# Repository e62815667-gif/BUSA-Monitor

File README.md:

# BUSA-Monitor

Исходные коды, интерфейсы, GitHub Actions и документация проекта «БУСА-1М №001».

## Актуальное состояние (15 ноября 2026)

**Ветка `main` — документация и текущая публикация. 22 активные ветки.** Исторические исходники всех 137 веток, находившихся в репозитории перед массовой очисткой, сохранены в проверенном Git-архиве.

- [Паспорт последней подтверждённой рабочей UI16](docs/UI16_VERIFIED_2026-11-15.md) — SHA-256, два BIN, статус проверки на оборудовании, ограничение по исходникам.
- [Актуальный реестр 22 веток](docs/BRANCH_INVENTORY_2026-11-15.md).
- [Полный отчёт об уборке](docs/REPOSITORY_AUDIT_2026-11-15.md).
- [Постоянный Git-архив из 137 веток](https://github.com/e62815667-gif/BUSA-Monitor/releases/tag/busa-git-backup-all-branches-20261115) — полный Git bundle, SHA, инструкция восстановления.
- [GitHub Actions](https://github.com/e62815667-gif/BUSA-Monitor/actions) — журналы сборок.
- [GitHub Releases](https://github.com/e62815667-gif/BUSA-Monitor/releases) — опубликованные релизы.
- [Открытые Pull Request](https://github.com/e62815667-gif/BUSA-Monitor/pulls) — 7 PR и все их необходимые ветки сохранены.
- [Правила проекта](PROJECT_RULES.md).

## Эталон UI16

**BUSA UI16 успешно установлена и работает на ESP32-S3 N16R8 по подтверждению владельца от 15.11.2026.** Оба BIN-файла (USB MERGED, APP OTA) находятся в Google Диске «успех буса». Контрольные суммы проверены.

Точная исходная ветка UI16 ещё не установлена. В GitHub сохранена более ранняя CALC4/WIFI1, но её нельзя автоматически считать исходниками UI16. Успешная сборка CI и работа прошивки на реальном устройстве — разные уровни проверки.

## Исторические ветки

140 → **22 активные**, 118 удалены из списка веток. Из них 115 удалены **после** создания и тестового восстановления постоянного Git-архива; первые 3 были точным дубликатом или принадлежали уже объединённым PR. Исходники доступны через восстановление из архива, не теряйте архивный релиз.

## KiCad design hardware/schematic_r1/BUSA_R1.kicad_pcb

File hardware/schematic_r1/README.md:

# БУСА — схема R1, 08.11.2026

Статус: **электрический проект, проверенный программно; не испытан на устройстве; не разрешение на производство PCB**. Основа — UI12 f80e8af, фактическая 44-контактная таблица ESP32 пользователя, фотографии модулей и уточнение VCC экрана = 3,3 В. Прошивка этой работой не менялась.

## Что изготовлено

- BUSA_R1.kicad_sch / BUSA_R1.kicad_pro / BUSA.kicad_sym / sym-lib-table — открываемый проект KiCad 9, с собственной библиотекой функциональных символов модулей.
- output/BUSA_R1_review.pdf — пояснения, разъёмы и схема по читаемым разделам.
- output/BUSA_R1.pdf — полный лист A1.
- output/NETLIST.xml и PIN_NETS.csv — список соединений, экспортированный KiCad.
- output/ERC.json — 0 ошибок, 0 предупреждений, исключений проверок нет.
- output/CHECKS.json — 10 независимых проверок экспортированных цепей; отрицательный контроль действительно обнаруживает соединение двух GPIO-выходов.
- output/BOM.csv и HEADER_44.csv — элементы и положение контактов ESP32. Наличие позиции в BOM не означает, что она уже есть у пользователя.
- BUSA_R1.kicad_pcb, BUSA.pretty, fp-lib-table и footprints.json — физический инженерный проект: 120 × 100 мм, два слоя, 67 электрических посадочных мест и четыре отверстия. Междурядье ESP32 25,50 мм взято с предоставленной пользователем переходной платы; шаг 2,54 мм — из его ответа. Геометрия PCF8575 пока предварительная.
- output/PCB_DRC.json, PCB_CHECKS.json и PCB_DRC_negative_control.json — полный DRC с сопоставлением схемы и платы, сверка 207 подключённых площадок по XML и испытание проверки настоящим коротким замыканием в временной копии.
- output/BUSA_R1_PCB_REVIEW.pdf, PCB_PREVIEW.png, MEASUREMENT_GUIDE.png, CONTROL_TEMPLATE_1TO1.pdf, BOM_REVIEW.csv, HARNESS.csv и ACCESSORIES.csv — документы для технической проверки. Это ещё не производственный FAB/ASSEMBLY.
- PRODUCTION.md и output/RELEASE_STATUS.json — выбранный изготовитель, проектные требования, состав будущего заказа и открытые условия готовности.

Символы пользовательских модулей являются функциональным описанием их выводов. Схемы внутри готовых модулей не воспроизведены и не проверены по изображению. Рисунок предыдущего эскиза не использовался как источник распиновки или размеров.

## Изменения по сравнению с картинкой

1. Вход питания J1 имеет ровно два контакта: 1 = +12 В, 2 = GND. Третьего провода нет.
2. ESP32 — настоящий вариант 44 PIN / два USB. Номера L01..L22 и R01..R22 идут сверху вниз при обоих USB наверху и виде на компоненты.
3. PCF8575 — готовый съёмный модуль, логика 3,3 В, SDA40/SCL41. INT не подключён. Клавиатура имеет девять сигнальных проводников.
4. Температуры: Вода GPIO16, Куб GPIO18, Колонна GPIO17, Авария GPIO21; по одной подтяжке 4,7 кОм и разъёму на канал, без DS2482. Порядок датчиков на разъёмах соответствует запрошенному отображению, а GPIO — текущей прошивке.
5. На модуль четырёх звуковых реле идут GND, IN1, IN2, IN3, IN4, VCC (шесть контактов логики); питание катушек JD-VCC проходит отдельно. Не путать эти линии с тремя переключаемыми контактами COM/NO/NC каждого реле. Силовые/сетевые нагрузки не входят в проект.
6. SN74LVC07A — новый, предлагаемый для несущей платы неинвертирующий буфер с открытым стоком. Сохраняет активный LOW из UI12, отводит 5 В от ESP32, обеспечивает подтяжки отключённого состояния. При выключенном питании логики используется Ioff по документации TI.
7. YF-S401 подключается через отдельный преобразователь уровня BC847B + триггер Шмитта, а не непосредственно к GPIO15. Сочетание двух инверсий сохраняет полярность и число импульсов. GPIO1 подготовлен только как аппаратный резерв отбора; в UI12 чтение отбора ещё не реализовано, модель датчика пока не выбрана.
8. Предлагаемый стабилизатор U2 R-78E5.0-1.0 — новая позиция для питания платы, а не выданная за имеющийся модуль с фотографии. Его можно заменить реальным существующим DC/DC только после установления модели, параметров и распиновки.

## Проверки, уже выполненные

KiCad 9.0.2 ERC без исключений: **0 нарушений**. Все соединения проверяются по NETLIST.xml, не только по внутренней модели генератора. Сверены 4 температурных канала, 5 TFT-сигналов, 4 релейных управляющих сигнала, I²C, питание и разделение каналов импульсов. USB19/20, PSRAM35/36/37 и загрузочные выводы оставлены неиспользованными.

Негативный тест: в временной копии GPIO7 соединён с GPIO14; KiCad вернул ошибку конфликта выходов. Исходный проект после теста остаётся без этого замыкания.

Для импульсного входа рассчитано: при источнике 4,5 В, резисторах с допуском 1% и предположении VBE=0,85 В базовый ток не менее 104 мкА, ток коллектора не более 0,702 мА, принудительный коэффициент около 6,72. Это проверка запаса насыщения для принятой модели входа, не замена измерению реального датчика. RC-цепь имеет постоянную времени менее 6 мкс против типового периода 1,7 мс при 588 Гц. Номинальные 98 Гц/(л/мин) взяты из существующей прошивки; их физическая точность не подтверждена.

Подтяжки R1/R2 I²C — опциональные. На готовом PCF8575 могут уже быть резисторы; до установки нужно проверить результирующее сопротивление к 3,3 В. Не устанавливать подтяжки к 5 В.

## Границы проверки и следующие измерения

- **Релейный модуль:** название SRD-12VDC-SL-C описывает реле, а не полную принципиальную схему платы. По текущим фото не определены все связи JD-VCC/трёхконтактной перемычки и возврата катушек. JP2 оставлен разомкнутым. До его замыкания проверить маркировку, отсутствие соединения VCC5 с JD12 и ток/полярность входов. Это условие не скрыто нулевым ERC.
- **Питание ESP32/USB:** JP1 отключает внешние 5 В. Перед питанием от любого USB разомкнуть JP1. Защита от любой комбинации одновременных источников не заявлена; внутреннюю схему USB вашего клона ещё требуется проверить.
- **3,3 В:** экран сейчас питается от 3,3 В по подтверждению пользователя. В R1 эта шина приходит от стабилизатора ESP32. Потребление TFT с подсветкой, PCF8575 и датчиков и допустимый нагрев конкретного стабилизатора не измерены. При недостаточном запасе потребуется отдельная правильно развязанная шина питания, а не соединение двух выходов стабилизаторов.
- **Посадочные места:** назначены проектные footprints и выполнена разводка. ESP32: шаг 2,54 мм и междурядье 25,50 мм по ответу/фото пользователя; корпус/USB/антенну проверить отпечатком 1:1. Для PCF8575 расположение трёх колодок не установлено, параметры заменяемые. Новые вертикальные кабельные JST XH имеют шаг 2,50 мм. Gerber и разрешённый комплект для заказа не выпускались.
- **Проводка датчиков:** J6–J9 задают новый порядок 1=VDD, 2=DQ, 3=GND. Цвета жил и порядок старых разъёмов проверить до сборки. J10/J11: 1=питание, 2=GND, 3=импульс. Не переставлять существующий штекер только по внешнему сходству.
- **Датчик отбора:** модель, напряжение, тип выхода, минимальный расход и коэффициент импульсов неизвестны. JP4 оставлен разомкнутым, GPIO1 не активируется новой прошивкой. Показания отбора этим проектом не становятся доступными автоматически.
- **Макетные испытания:** фактические уровни/выбросы, нагрев, помехоустойчивость длинных кабелей и работа при включении/отключении не испытаны. Все земли проекта общие; гальваническая развязка не заявлена. Проект рассчитан на регулируемые 12 В DC, не на автомобильную/промышленную сеть с неограниченными выбросами.

## Повтор проверки

Запустить tools/run_checks.sh из любого каталога. Нужны Python, KiCad 9, ReportLab и PyMuPDF для оформления PDF. Генератор детерминирован; отрицательный контроль выполняется во временном каталоге. Все исходные файлы и результаты включены в локальный проект.

Полная текущая проверка: `bash tools/check_pcb.sh`. Для PCB нужен системный Python с pcbnew и Matplotlib. Скрипт завершится кодом 2 на проверке выпуска, пока реальные данные из `pcb_parameters.json` и выбор MPN не подтверждены. ERC/DRC и отсутствие обрывов проверяются до этого отдельно. `pcb_build.py` перезаписывает разводку исходным размещением: применять его только при изменении геометрии, затем заново трассировать и проверять.

Маршруты рассчитаны локально Freerouting 2.0.1 (официальный релиз, совместим с установленным Java 21); данные в онлайн-сервис не отправлялись. При переносе результата снят один лишний переход V3V3, который не соединял разные слои. Окончательная чистота подтверждена KiCad, а не отчётом трассировщика.

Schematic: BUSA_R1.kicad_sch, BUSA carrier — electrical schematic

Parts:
C1: 10uF / 35V; C_1210_3225Metric
C2: 100nF / 50V; C_0805_2012Metric
C3: 10uF / 10V; C_1210_3225Metric
C4, C5, C7, C9, C10, C11, C12, C13, C16: 100nF; C_0805_2012Metric
C6: 10uF / 6.3V; C_0805_2012Metric
C8: 4.7uF; C_0805_2012Metric
C14, C15: 1nF; C_0805_2012Metric
D1: B340A-13-F / SMA; D_SMA_LOGICAL_A_K
D2, D3: 1N4148W; 1N4148W_SOD123_LOGICAL_A_K
F1: 1A slow / 32V; Fuse_Littelfuse_NANO2_454_DRAFT
J1: DC INPUT / 12V ONLY; JST_XH_B2B-XH-A_1x02_P2.50mm_Vertical
J2: TFT / VCC=3.3V; JST_XH_B7B-XH-A_1x07_P2.50mm_Vertical
J3: KEYPAD 9-WIRE; JST_XH_B9B-XH-A_1x09_P2.50mm_Vertical
J4: RELAY CTRL / 6; JST_XH_B6B-XH-A_1x06_P2.50mm_Vertical
J5: COIL SUPPLY / 2; JST_XH_B2B-XH-A_1x02_P2.50mm_Vertical
J6: DS18B20 WATER; JST_XH_B3B-XH-A_1x03_P2.50mm_Vertical
J7: DS18B20 CUBE; JST_XH_B3B-XH-A_1x03_P2.50mm_Vertical
J8: DS18B20 COLUMN; JST_XH_B3B-XH-A_1x03_P2.50mm_Vertical
J9: DS18B20 ALARM; JST_XH_B3B-XH-A_1x03_P2.50mm_Vertical
J10: COOL PULSE / 3; JST_XH_B3B-XH-A_1x03_P2.50mm_Vertical
J11: COL PULSE / 3; JST_XH_B3B-XH-A_1x03_P2.50mm_Vertical
J12: BUZZER LOGIC ONLY; JST_XH_B2B-XH-A_1x02_P2.50mm_Vertical
JP1: ESP PWR LINK / OPEN; PinHeader_1x02_P2.54mm_Vertical
JP2: JD12 LINK / OPEN; PinHeader_1x02_P2.54mm_Vertical
JP3: COOL PWR LINK / OPEN; PinHeader_1x02_P2.54mm_Vertical
JP4: COL PWR LINK / OPEN; PinHeader_1x02_P2.54mm_Vertical
PF1, PF2, PF3, PF4: POWER_FLAG
Q1, Q2: BC847B / SOT23; SOT-23
R1, R2: 4.7k OPTIONAL; R_0805_2012Metric; not fitted
R11, R12, R13, R14, R41, R51: 10k; R_0805_2012Metric
R21, R22, R23, R24, R30, R31, R32, R33, R44, R54: 4.7k; R_0805_2012Metric
R42, R52: 22k; R_0805_2012Metric
R43, R53: 100k; R_0805_2012Metric
R45, R55: 330; R_0805_2012Metric
U1: ESP32-S3 / user 44PIN; ESP32S3_44PIN_SOCKET_DRAFT
U2: R-78E5.0-1.0; RECOM_R78E10_11.6x8.5_P2.54
U3: PCF8575 MODULE / 8+8+5; PCF8575_8_8_5_SOCKET_DRAFT
U4: SN74LVC07AD / SOIC14; SOIC-14_3.9x8.7mm_P1.27mm
U5: SN74LVC2G14DBV / SOT23-6; SOT-23-6

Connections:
/BUZZER_SIG: J12.1 (GPIO2), U1.L18 (GPIO2)
/COLLECT_GPIO1: R55.2, U1.L19 (GPIO1)
/COL_BASE: D3.K (CATHODE), Q2.1 (B), R52.2, R53.1
/COL_BUF: R55.1, U5.4 (2Y)
/COL_COL: C15.1, Q2.3 (C), R54.2, U5.3 (2A)
/COL_PWR: J11.1 (V_SENSOR), JP4.2, R51.1
/COL_RAW: J11.3 (PULSE), R51.2, R52.1
/COOL_BASE: D2.K (CATHODE), Q1.1 (B), R42.2, R43.1
/COOL_BUF: R45.1, U5.6 (1Y)
/COOL_COL: C14.1, Q1.3 (C), R44.2, U5.1 (1A)
/COOL_GPIO15: R45.2, U1.R15 (GPIO15)
/COOL_PWR: J10.1 (V_SENSOR), JP3.2, R41.1
/COOL_RAW: J10.3 (PULSE), R41.2, R42.1
/ESP_5V: JP1.2, PF4.1, U1.R02 (5V)
/GND: C1.2, C2.2, C3.2, C4.2, C5.2, C6.2, C7.2, C8.2, C9.2, C10.2, C11.2, C12.2, C13.2, C14.2, C15.2, C16.2, D2.A (ANODE), D3.A (ANODE), J1.2 (GND), J2.1 (GND), J4.1 (GND), J5.2 (GND_RETURN), J6.3 (GND), J7.3 (GND), J8.3 (GND), J9.3 (GND), J10.2 (GND), J11.2 (GND), J12.2 (GND), PF2.1, Q1.2 (E), Q2.2 (E), R43.2, R53.2, U1.L01 (GND), U1.L02 (GND), U1.L22 (GND), U1.R01 (GND), U2.2 (GND), U3.GND, U4.7 (GND), U4.11 (5A), U4.13 (6A), U5.2 (GND)
/I2C_SCL: R2.2, U1.L16 (GPIO41), U3.SCL
/I2C_SDA: R1.2, U1.L15 (GPIO40), U3.SDA
/K1_GPIO7: R11.2, U1.R16 (GPIO7), U4.1 (1A)
/K2_GPIO6: R12.2, U1.R17 (GPIO6), U4.3 (2A)
/K3_GPIO5: R13.2, U1.R18 (GPIO5), U4.5 (3A)
/K4_GPIO4: R14.2, U1.R19 (GPIO4), U4.9 (4A)
/KEY1: J3.1, U3.P00
/KEY2: J3.2, U3.P01
/KEY3: J3.3, U3.P02
/KEY4: J3.4, U3.P03
/KEY5: J3.5, U3.P04
/KEY6: J3.6, U3.P05
/KEY7: J3.7, U3.P06
/KEY8: J3.8, U3.P07
/KEY9: J3.9, U3.P10
/RELAY_IN1: J4.2 (IN1), R21.2, U4.2 (1Y OD)
/RELAY_IN2: J4.3 (IN2), R22.2, U4.4 (2Y OD)
/RELAY_IN3: J4.4 (IN3), R23.2, U4.6 (3Y OD)
/RELAY_IN4: J4.5 (IN4), R24.2, U4.8 (4Y OD)
/RELAY_JD12: J5.1 (JD_VCC), JP2.2
/TEMP_ALARM: J9.2 (DQ), R33.2, U1.L05 (GPIO21)
/TEMP_COLUMN: J8.2 (DQ), R32.2, U1.R13 (GPIO17)
/TEMP_CUBE: J7.2 (DQ), R31.2, U1.R12 (GPIO18)
/TEMP_WATER: J6.2 (DQ), R30.2, U1.R14 (GPIO16)
/TFT_CS: J2.7 (CS), U1.R07 (GPIO10)
/TFT_DC: J2.6 (DC), U1.R06 (GPIO11)
/TFT_MOSI: J2.4 (SDA_MOSI), U1.R04 (GPIO13)
/TFT_RST: J2.5 (RST), U1.R05 (GPIO12)
/TFT_SCK: J2.3 (SCK), U1.R03 (GPIO14)
/V3V3: C5.1, C6.1, C7.1, C8.1, C9.1, C10.1, C11.1, C12.1, C13.1, C16.1, J2.2 (VCC), J6.1 (VDD), J7.1 (VDD), J8.1 (VDD), J9.1 (VDD), R1.1, R2.1, R11.1, R12.1, R13.1, R14.1, R30.1, R31.1, R32.1, R33.1, R44.1, R54.1, U1.R21 (3V3), U1.R22 (3V3), U3.VCC, U4.14 (VCC), U5.5 (VCC)
/V5: C3.1, C4.1, J4.6 (VCC), JP1.1, JP3.1, JP4.1, R21.1, R22.1, R23.1, R24.1, U2.3 (5V OUT)
/V12_PROT: C1.1, C2.1, D1.K (CATHODE), JP2.1, PF3.1, U2.1 (VIN)
/VIN12: F1.1, J1.1 (+12V), PF1.1
/VIN12_FUSED: D1.A (ANODE), F1.2

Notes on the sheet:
БУСА R1 — электрическая схема модульной несущей платы
СВЕРКА С UI12 / ERC / ПОДГОТОВКА К МАКЕТУ. На устройстве не испытано.
Назначения выводов по маркировке; посадочные места и обратные стороны модулей ещё требуется проверить.
1. Питание: 12 В, два контакта
JP1 снять перед питанием/прошивкой от USB.
3,3 В — от ESP32. Ток с экраном измерить.
12 В не подавать на VCC логики или GPIO.
2. ESP32-S3 N16R8: 44 контакта
GPIO1 — резерв. UI12 ещё не считывает отбор.
USB 19/20, PSRAM 35–37 и boot-пины оставлены свободными.
3. Экран GMT028-05 V1.1
VCC=3,3 В подтверждено владельцем.
GPIO взяты из UI12, не из старых схем октября.
4. PCF8575 — готовый съёмный модуль
Шлейф клавиатуры: девять сигнальных линий.
Нумерацию и ориентацию шлейфа сверить. Питания в нём нет.
5. Температуры: напрямую к ESP32
Четыре независимые линии DQ, четыре подтяжки.
3-проводное питание, не паразитный режим.
Цвета жил датчиков не заменяют проверку распиновки.
6. Реле: буфер сохраняет активный LOW
J4 — 6 контактов логики. J5 — 2 линии питания катушек.
На модуле снять перемычку VCC/JD-VCC. Нельзя замкнуть 12 В с 5 В.
JP2 по умолчанию разомкнут до проверки маркировки и питания.
7. Два импульсных входа: защита уровня + триггер Шмитта
GPIO15: охлаждение. GPIO1: аппаратный резерв отбора.
У входа два инвертора: Q + U5. Полярность импульса сохраняется.
Отбор UI12 не поддерживает; нужна отдельная доработка ПО.
Все земли общие. Гальваническая развязка не заявлена.
R1: до разводки PCB подтвердить размеры модулей, распиновку JD-VCC, ток 3,3 В и датчик отбора.

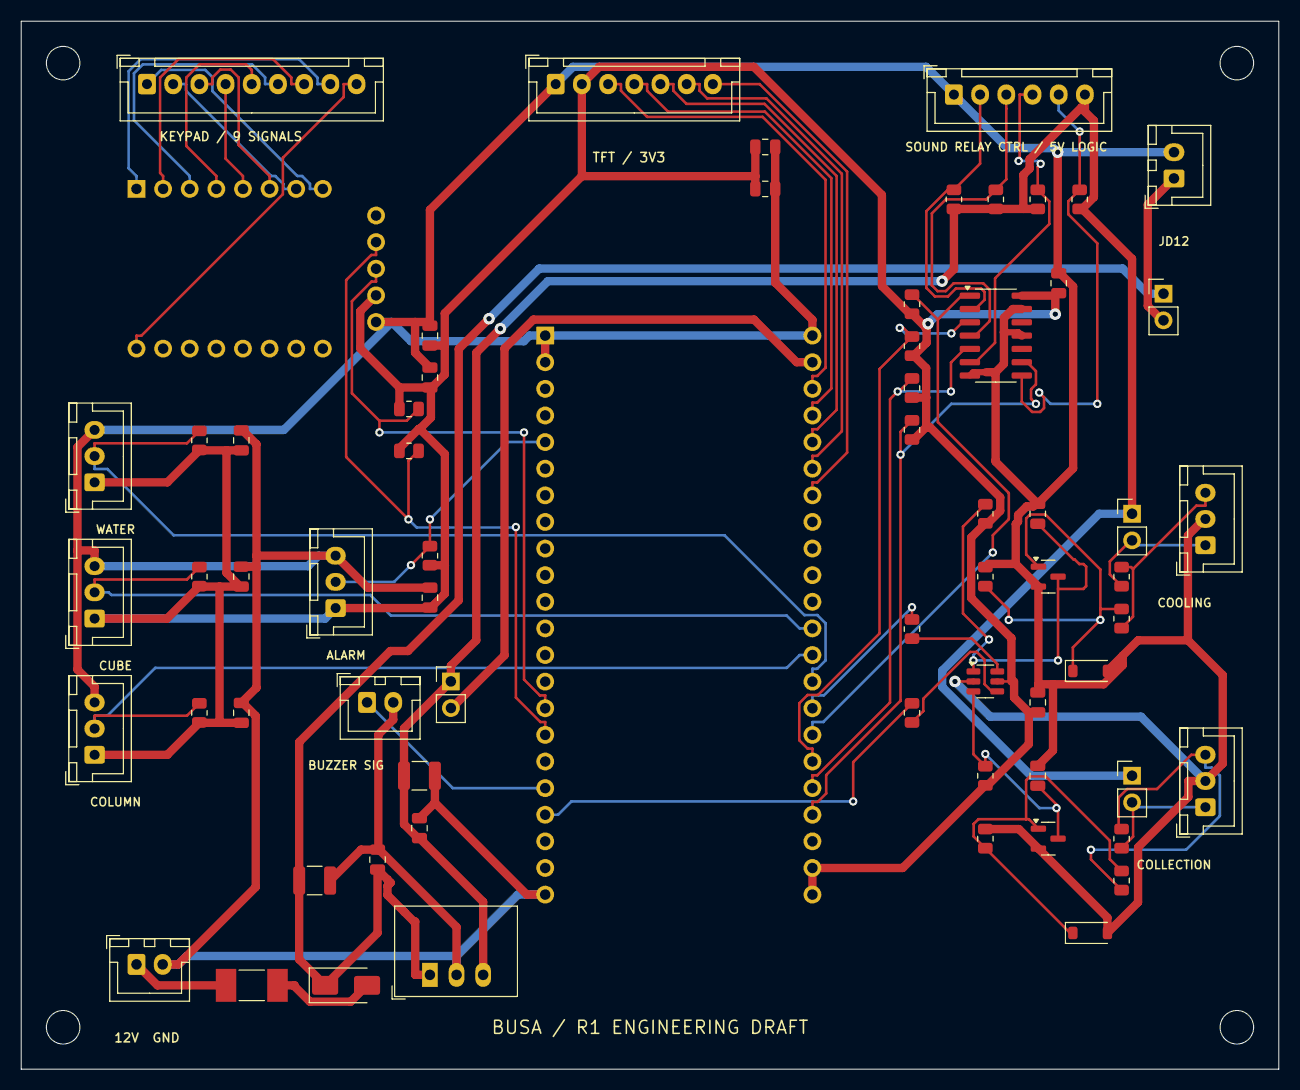
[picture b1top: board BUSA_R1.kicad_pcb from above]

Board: 2 copper layers, 120.0 x 100.0 mm, 71 parts (0 on the bottom side), 49 nets.

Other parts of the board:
H1, H2, H3, H4: MountingHole_3.2mm_M3

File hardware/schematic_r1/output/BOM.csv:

Ref,Value,Kind,Datasheet,Notes
J1,DC INPUT / 12V ONLY,Proposed carrier part/connector,,
F1,1A slow / 32V,Proposed carrier part/connector,,
D1,B340A-13-F / SMA,Proposed carrier part/connector,https://www.diodes.com/datasheet/download/B340A.pdf,Exact SMA Schottky choice; do not substitute a vendor SS34 in SMC
U2,R-78E5.0-1.0,Proposed carrier part/connector,https://recom-power.com/pdf/Innoline/R-78E-1.0.pdf,"New selected regulator option, not claimed existing user component"
C1,10uF / 35V,Proposed carrier part/connector,,
C2,100nF / 50V,Proposed carrier part/connector,,
C3,10uF / 10V,Proposed carrier part/connector,,
C4,100nF,Proposed carrier part/connector,,
JP1,ESP PWR LINK / OPEN,Open by default; see commissioning conditions,,Open before either ESP32 USB port is powered. Do not connect external 5V and USB concurrently.
U1,ESP32-S3 / user 44PIN,Existing user module,,L/R numbered top-to-bottom with both USB at top. Actual socket geometry still to measure.
J12,BUZZER LOGIC ONLY,Proposed carrier part/connector,,Logic control only; not direct supply for a bare buzzer
J2,TFT / VCC=3.3V,Proposed carrier part/connector,,New carrier pin order matches photographed display legends; confirm cable face/orientation
C5,100nF,Proposed carrier part/connector,,
C6,10uF / 6.3V,Proposed carrier part/connector,,
U3,PCF8575 MODULE / 8+8+5,Existing user module,,"Pin numbers are actual printed terminal names, not invented physical positions. INT and 7 unused I/O are NC."
J3,KEYPAD 9-WIRE,Proposed carrier part/connector,,Harness 1..8 -> P00..P07; 9 -> P10. Preserve installed harness mapping or retrain.
R1,4.7k OPTIONAL,Optional - check module pullups before fitting,,Measure existing module pullups first; effective target 2.2k..10k to 3.3V only
R2,4.7k OPTIONAL,Optional - check module pullups before fitting,,Measure existing module pullups first; no 5V pullup
C7,100nF,Proposed carrier part/connector,,
C8,4.7uF,Proposed carrier part/connector,,
J6,DS18B20 WATER,Proposed carrier part/connector,,"Carrier standard: 1=VDD,2=DQ,3=GND; identify actual cable conductors before crimping"
R30,4.7k,Proposed carrier part/connector,,
C10,100nF,Proposed carrier part/connector,,
J7,DS18B20 CUBE,Proposed carrier part/connector,,"Carrier standard: 1=VDD,2=DQ,3=GND; identify actual cable conductors before crimping"
R31,4.7k,Proposed carrier part/connector,,
C11,100nF,Proposed carrier part/connector,,
J8,DS18B20 COLUMN,Proposed carrier part/connector,,"Carrier standard: 1=VDD,2=DQ,3=GND; identify actual cable conductors before crimping"
R32,4.7k,Proposed carrier part/connector,,
C12,100nF,Proposed carrier part/connector,,
J9,DS18B20 ALARM,Proposed carrier part/connector,,"Carrier standard: 1=VDD,2=DQ,3=GND; identify actual cable conductors before crimping"
R33,4.7k,Proposed carrier part/connector,,
C13,100nF,Proposed carrier part/connector,,
U4,SN74LVC07AD / SOIC14,Proposed carrier part/connector,https://www.ti.com/lit/ds/symlink/sn74lvc07a.pdf,Noninverting open-drain; outputs tolerate 5.5V; Ioff; GPIO low => sink relay IN low
J4,RELAY CTRL / 6,Proposed carrier part/connector,,Matches photographed legends GND IN1 IN2 IN3 IN4 VCC. Check physical orientation.
R11,10k,Proposed carrier part/connector,,Reset pullup: relay OFF
R21,4.7k,Proposed carrier part/connector,,Logic pullup only; not coil supply
R12,10k,Proposed carrier part/connector,,Reset pullup: relay OFF
R22,4.7k,Proposed carrier part/connector,,Logic pullup only; not coil supply
R13,10k,Proposed carrier part/connector,,Reset pullup: relay OFF
R23,4.7k,Proposed carrier part/connector,,Logic pullup only; not coil supply
R14,10k,Proposed carrier part/connector,,Reset pullup: relay OFF
R24,4.7k,Proposed carrier part/connector,,Logic pullup only; not coil supply
C9,100nF,Proposed carrier part/connector,,
JP2,JD12 LINK / OPEN,Open by default; see commissioning conditions,,Identify actual JD-VCC and remove module VCC/JD jumper BEFORE closing
J5,COIL SUPPLY / 2,Proposed carrier part/connector,,New carrier connector; actual relay-board JD header pin order/return requires measurement
J10,COOL PULSE / 3,Proposed carrier part/connector,,"Carrier order 1=power,2=GND,3=pulse. Cooling: YF-S401. Collection model unspecified."
JP3,COOL PWR LINK / OPEN,Open by default; see commissioning conditions,,Populate only after verifying sensor supply; collection model remains open
R41,10k,Proposed carrier part/connector,,Pullup supports open-collector sensor; inspect push-pull compatibility
R42,22k,Proposed carrier part/connector,,
Q1,BC847B / SOT23,Proposed carrier part/connector,https://assets.nexperia.com/documents/data-sheet/BC847X_SER.pdf,
R43,100k,Proposed carrier part/connector,,
R44,4.7k,Proposed carrier part/connector,,
C14,1nF,Proposed carrier part/connector,,
D2,1N4148W,Proposed carrier part/connector,,
J11,COL PULSE / 3,Proposed carrier part/connector,,"Carrier order 1=power,2=GND,3=pulse. Cooling: YF-S401. Collection model unspecified."
JP4,COL PWR LINK / OPEN,Open by default; see commissioning conditions,,Populate only after verifying sensor supply; collection model remains open
R51,10k,Proposed carrier part/connector,,Pullup supports open-collector sensor; inspect push-pull compatibility
R52,22k,Proposed carrier part/connector,,
Q2,BC847B / SOT23,Proposed carrier part/connector,https://assets.nexperia.com/documents/data-sheet/BC847X_SER.pdf,
R53,100k,Proposed carrier part/connector,,
R54,4.7k,Proposed carrier part/connector,,
C15,1nF,Proposed carrier part/connector,,
D3,1N4148W,Proposed carrier part/connector,,
U5,SN74LVC2G14DBV / SOT23-6,Proposed carrier part/connector,https://www.ti.com/lit/ds/symlink/sn74lvc2g14.pdf,
R45,330,Proposed carrier part/connector,,
R55,330,Proposed carrier part/connector,,
C16,100nF,Proposed carrier part/connector,,
